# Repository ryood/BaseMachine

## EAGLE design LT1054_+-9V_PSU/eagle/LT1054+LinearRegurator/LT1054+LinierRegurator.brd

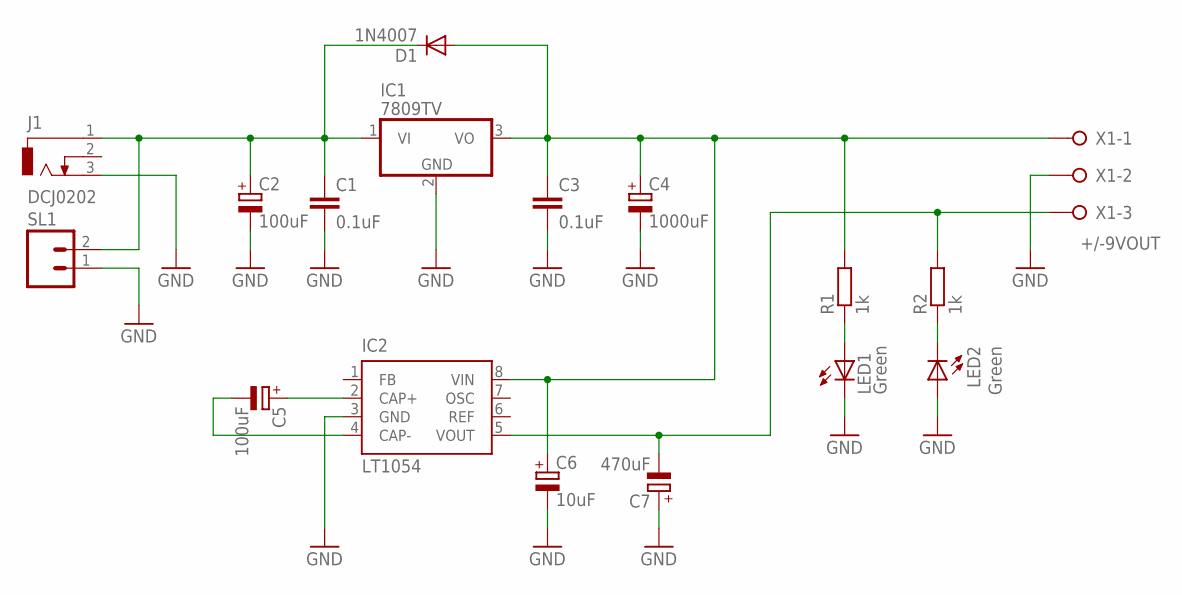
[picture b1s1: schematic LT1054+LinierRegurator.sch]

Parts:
C1, C3: 0.1uF; C025-024X044
C2, C5: 100uF; E2,5-7
C4: 1000uF; E5-13
C6: 10uF; E2,5-5
C7: 470uF; E5-8,5
D1: 1N4007; DO41-10
IC1: 7809TV; TO220V
IC2: LT1054; DIL8
J1: DCJ0202
LED1, LED2: Green; LED3MM
R1, R2: 1k; 0207/7
SL1: M02; 02P
X1: +/-9VOUT; W237-3E

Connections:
GND: C1.2, C2.-, C3.2, C4.-, C6.-, C7.+, IC1.2 (GND), IC2.3 (GND), J1.3, LED1.K (C), LED2.A, SL1.1, X1.2
unnamed: C1.1, C2.+, D1.C, IC1.1 (VI), J1.1, SL1.2
unnamed: C3.1, C4.+, C6.+, D1.A, IC1.3 (VO), IC2.8 (VIN), R1.2, X1.1
unnamed: C5.-, IC2.4 (CAP-)
unnamed: C5.+, IC2.2 (CAP+)
unnamed: C7.-, IC2.5 (VOUT), R2.2, X1.3
unnamed: LED1.A, R1.1
unnamed: LED2.K (C), R2.1

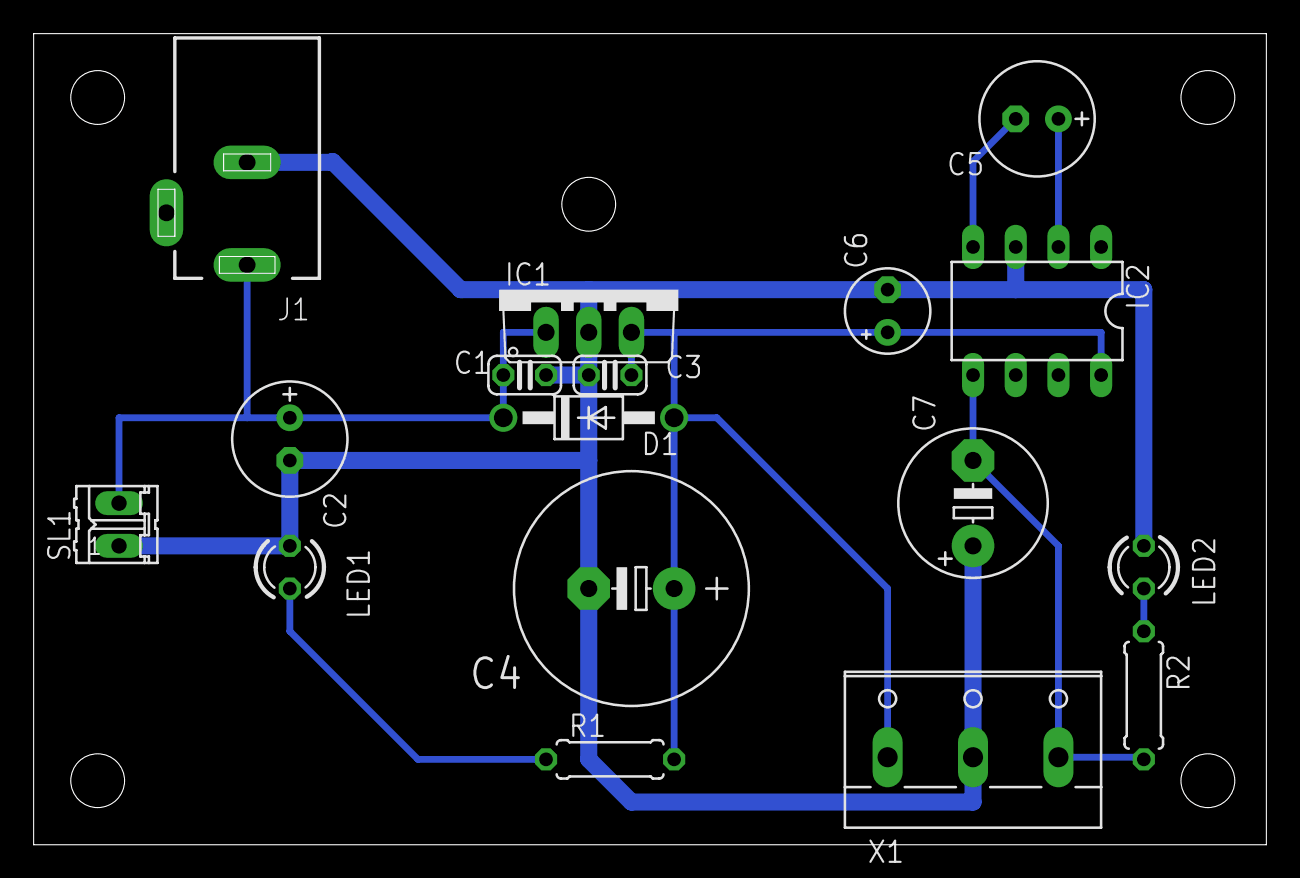
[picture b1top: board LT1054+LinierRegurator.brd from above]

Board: 2 copper layers, 73.3 x 48.2 mm, 17 parts (0 on the bottom side), 8 nets.

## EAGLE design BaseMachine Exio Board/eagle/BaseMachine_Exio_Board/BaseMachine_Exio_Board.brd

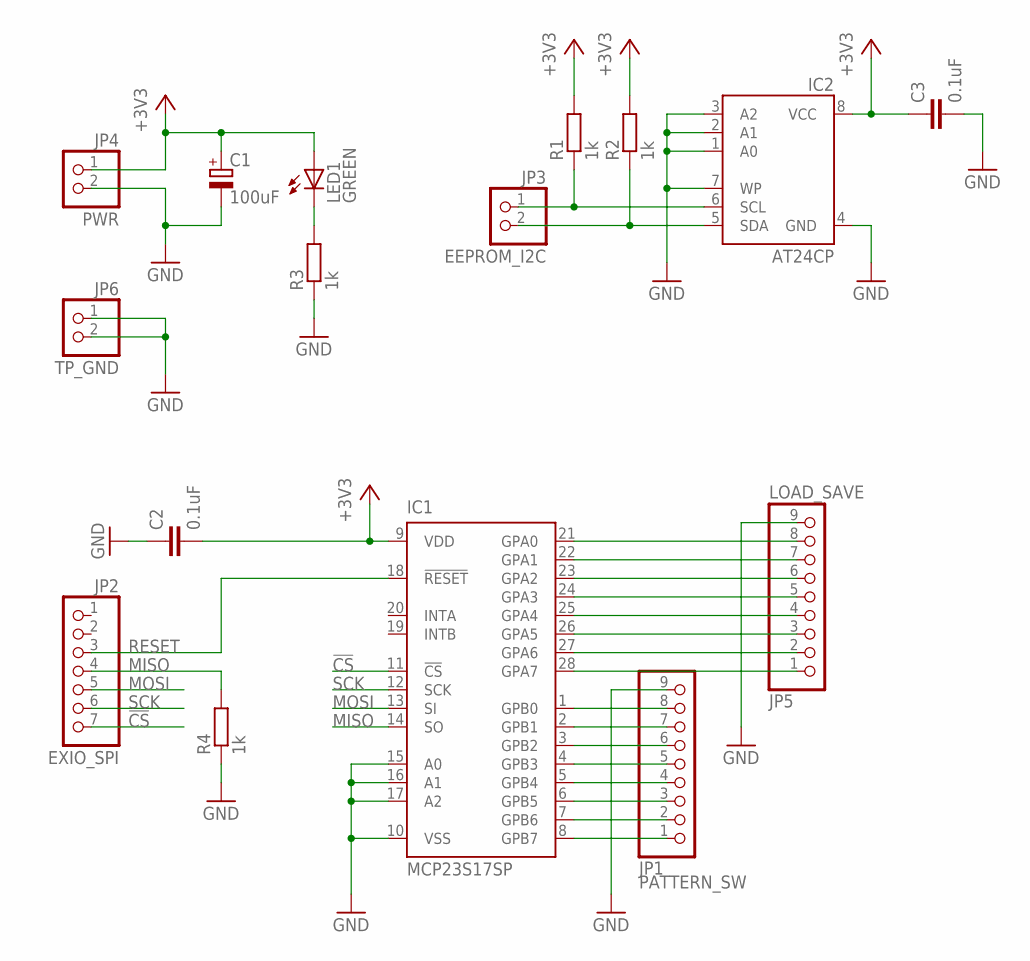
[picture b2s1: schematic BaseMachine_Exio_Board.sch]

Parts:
C1: 100uF; SANYO-OSCON_C6
C2, C3: 0.1uF; C025-024X044
IC1: MCP23S17SP; DIL28-3
IC2: AT24CP; DIL08
JP1: PATTERN_SW; 1X09/90
JP2: EXIO_SPI; 1X07/90
JP3: EEPROM_I2C; 1X02/90
JP4: PWR; 1X02/90
JP5: LOAD_SAVE; 1X09/90
JP6: TP_GND; 1X02
LED1: GREEN; LED3MM
R1, R2, R3, R4: 1k; 0207/7

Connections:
!CS: IC1.11 (!CS), JP2.7
+3V3: C1.+, C2.2, C3.1, IC1.9 (VDD), IC2.8 (VCC), JP4.1, LED1.A, R1.2, R2.2
GND: C1.-, C2.1, C3.2, IC1.10 (VSS), IC1.15 (A0), IC1.16 (A1), IC1.17 (A2), IC2.1 (A0), IC2.2 (A1), IC2.3 (A2), IC2.4 (GND), IC2.7 (WP), JP1.9, JP4.2, JP5.9, JP6.1, JP6.2, R3.1, R4.1
MISO: IC1.14 (SO), JP2.4, R4.2
MOSI: IC1.13 (SI), JP2.5
unnamed: IC1.1 (GPB0), JP1.8
unnamed: IC1.2 (GPB1), JP1.7
unnamed: IC1.3 (GPB2), JP1.6
unnamed: IC1.4 (GPB3), JP1.5
unnamed: IC1.5 (GPB4), JP1.4
unnamed: IC1.6 (GPB5), JP1.3
unnamed: IC2.6 (SCL), JP3.1, R1.1
unnamed: IC2.5 (SDA), JP3.2, R2.1
unnamed: IC1.7 (GPB6), JP1.2
unnamed: IC1.21 (GPA0), JP5.8
unnamed: IC1.22 (GPA1), JP5.7
unnamed: IC1.23 (GPA2), JP5.6
unnamed: IC1.8 (GPB7), JP1.1
unnamed: IC1.24 (GPA3), JP5.5
unnamed: IC1.25 (GPA4), JP5.4
unnamed: IC1.26 (GPA5), JP5.3
unnamed: LED1.K (C), R3.2
unnamed: IC1.27 (GPA6), JP5.2
unnamed: IC1.28 (GPA7), JP5.1
RESET: IC1.18 (!RESET), JP2.3
SCK: IC1.12 (SCK), JP2.6

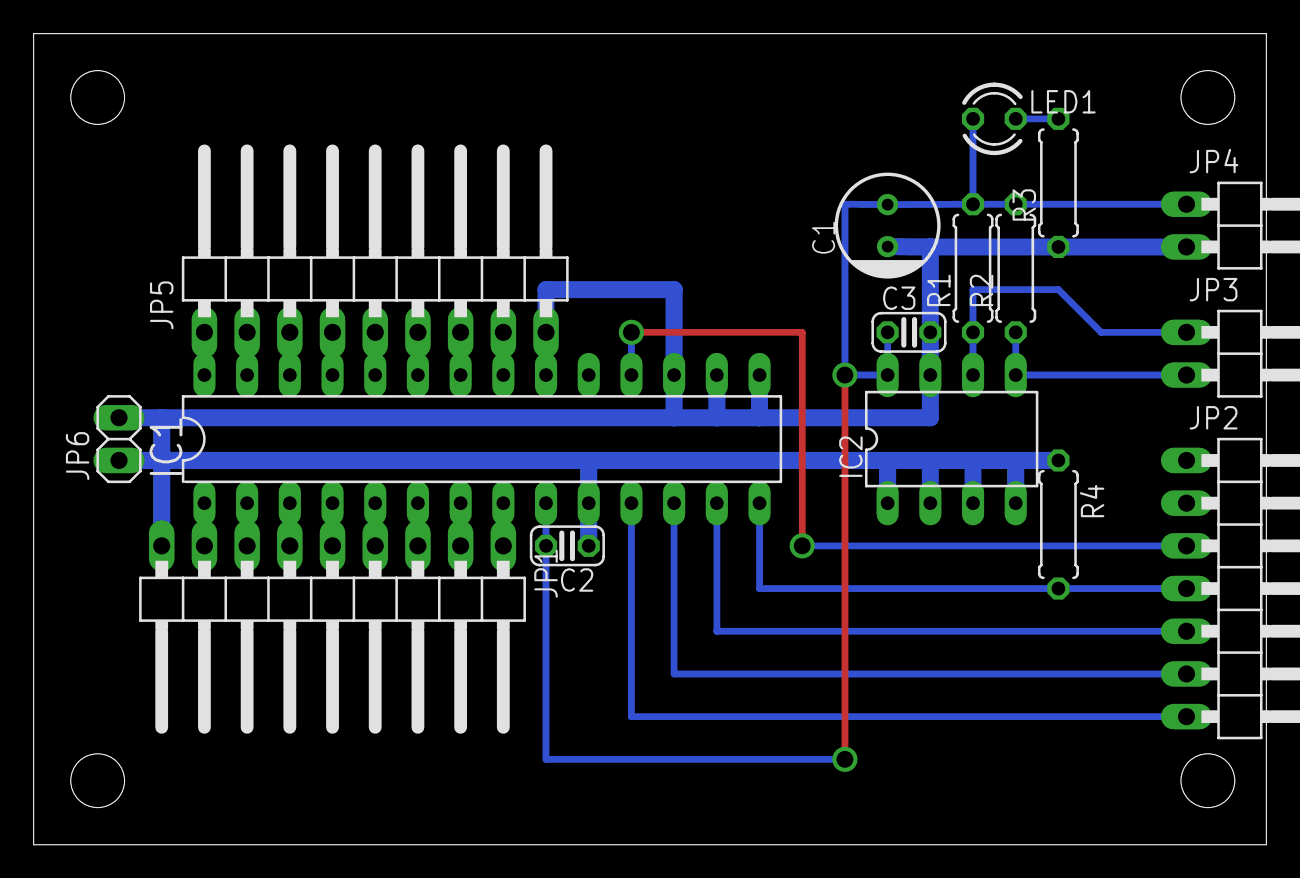
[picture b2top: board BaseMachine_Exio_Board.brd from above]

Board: 2 copper layers, 73.3 x 48.2 mm, 16 parts (0 on the bottom side), 26 nets.

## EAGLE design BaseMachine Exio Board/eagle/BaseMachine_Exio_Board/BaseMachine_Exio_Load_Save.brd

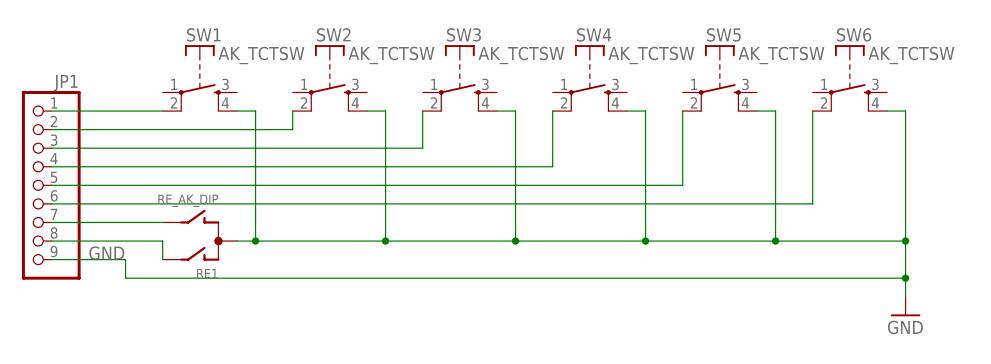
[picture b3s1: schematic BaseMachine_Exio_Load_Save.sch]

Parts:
JP1: PINHD-1X9; 1X09
RE1: RE_AK_DIP
SW1, SW2, SW3, SW4, SW5, SW6: AK_TCTSW; TME1

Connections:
GND: JP1.9, RE1.P$3 (C), SW1.4 (S), SW2.4 (S), SW3.4 (S), SW4.4 (S), SW5.4 (S), SW6.4 (S)
unnamed: JP1.1, SW1.2
unnamed: JP1.2, SW2.2
unnamed: JP1.3, SW3.2
unnamed: JP1.4, SW4.2
unnamed: JP1.5, SW5.2
unnamed: JP1.6, SW6.2
unnamed: JP1.7, RE1.P$4 (B)
unnamed: JP1.8, RE1.P$2 (A)

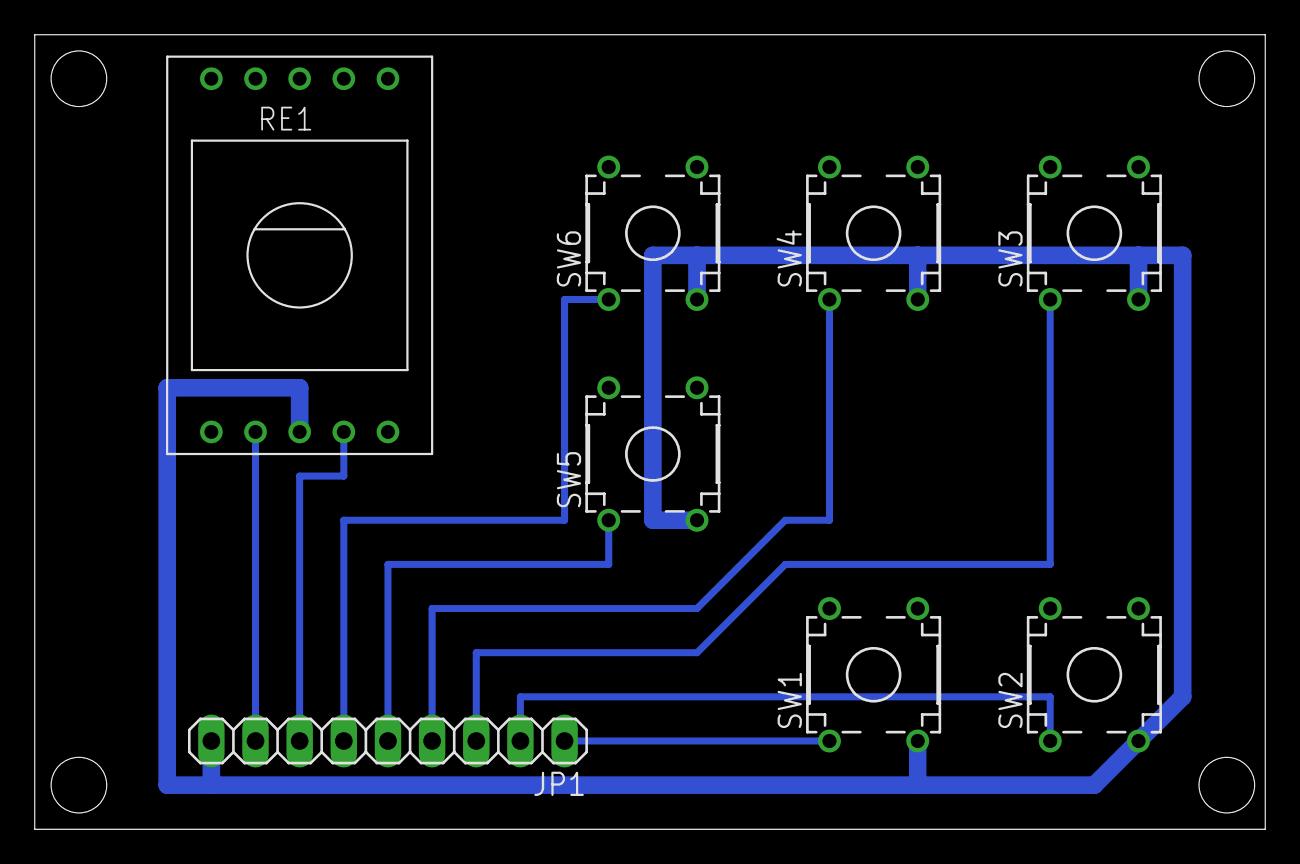
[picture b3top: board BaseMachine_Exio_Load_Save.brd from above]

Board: 2 copper layers, 70.8 x 45.7 mm, 8 parts (0 on the bottom side), 9 nets.

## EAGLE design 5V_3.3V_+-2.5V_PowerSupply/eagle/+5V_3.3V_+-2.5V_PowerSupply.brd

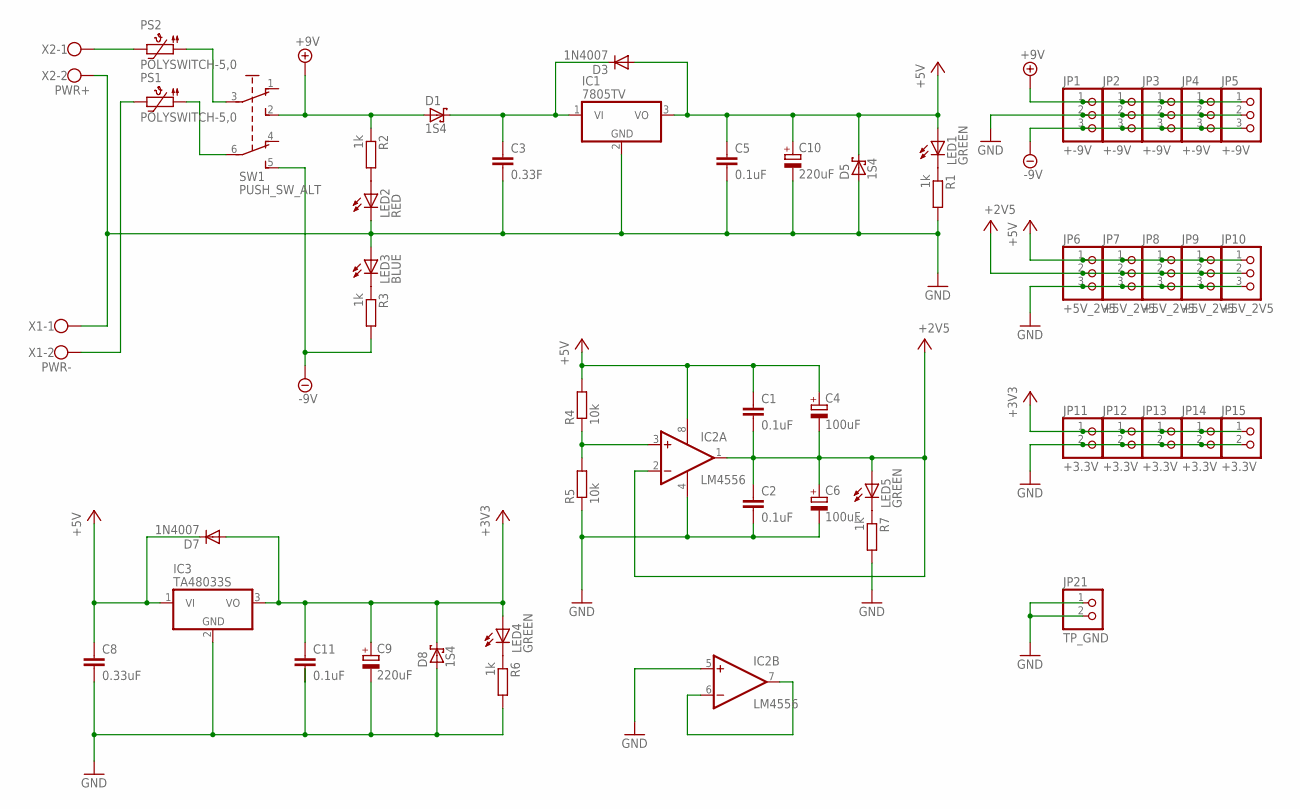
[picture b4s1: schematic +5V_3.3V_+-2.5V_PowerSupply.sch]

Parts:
C1, C2, C5, C11: 0.1uF; C025-024X044
C3: 0.33F; C050-025X075
C4, C6: 100uF; E2,5-6
C8: 0.33uF; C050-025X075
C9, C10: 220uF; E2,5-7
D1, D5, D8: 1S4; DO35-7
D3, D7: 1N4007; D-7.5
IC1: 7805TV; TO220V
IC2: LM4556; DIL08
IC3: TA48033S; TO220V
JP1, JP2, JP3, JP4, JP5: +-9V; 1X03
JP6, JP7, JP8, JP9, JP10: +5V_2V5; 1X03
JP11, JP12, JP13, JP14, JP15: +3.3V; 1X02
JP21: TP_GND; 1X02
LED1, LED4, LED5: GREEN; LED3MM
LED2: RED; LED3MM
LED3: BLUE; LED3MM
PS1, PS2: POLYSWITCH-5,0
R1, R2, R3, R6, R7: 1k; 0207/7
R4, R5: 10k; 0207/7
SW1: PUSH_SW_ALT
X1: PWR-; W237-102
X2: PWR+; W237-102

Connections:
+3V3: C9.+, C11.1, D7.A, D8.C, IC3.3 (VO), JP11.1, JP12.1, JP13.1, JP14.1, JP15.1, LED4.A
+5V: C1.1, C4.+, C5.1, C8.1, C10.+, D3.A, D5.C, D7.C, IC1.3 (VO), IC2.8 (V+), IC3.1 (VI), JP6.1, JP7.1, JP8.1, JP9.1, JP10.1, LED1.A, R4.2
+9V: D1.A, JP1.1, JP2.1, JP3.1, JP4.1, JP5.1, R2.1, SW1.2 (S)
-9V: JP1.3, JP2.3, JP3.3, JP4.3, JP5.3, R3.2, SW1.5 (S1)
GND: C2.2, C3.2, C5.2, C6.-, C8.2, C9.-, C10.-, C11.2, D5.A, D8.A, IC1.2 (GND), IC2.4 (V-), IC2.5 (+IN), IC3.2 (GND), JP1.2, JP2.2, JP3.2, JP4.2, JP5.2, JP6.3, JP7.3, JP8.3, JP9.3, JP10.3, JP11.2, JP12.2, JP13.2, JP14.2, JP15.2, JP21.1, JP21.2, LED2.K (C), LED3.A, R1.2, R5.1, R6.2, R7.2, X1.1, X2.2
unnamed: PS2.2, X2.1
unnamed: PS1.1, SW1.6 (P1)
unnamed: LED1.K (C), R1.1
unnamed: LED2.A, R2.2
unnamed: C3.1, D1.C, D3.C, IC1.1 (VI)
unnamed: LED3.K (C), R3.1
unnamed: IC2.3 (+IN), R4.1, R5.2
unnamed: LED5.K (C), R7.1
unnamed: IC2.6 (-IN), IC2.7 (OUT)
unnamed: PS1.2, X1.2
unnamed: PS2.1, SW1.3
unnamed: LED4.K (C), R6.1
V+: C1.2, C2.1, C4.-, C6.+, IC2.1 (OUT), IC2.2 (-IN), JP6.2, JP7.2, JP8.2, JP9.2, JP10.2, LED5.A

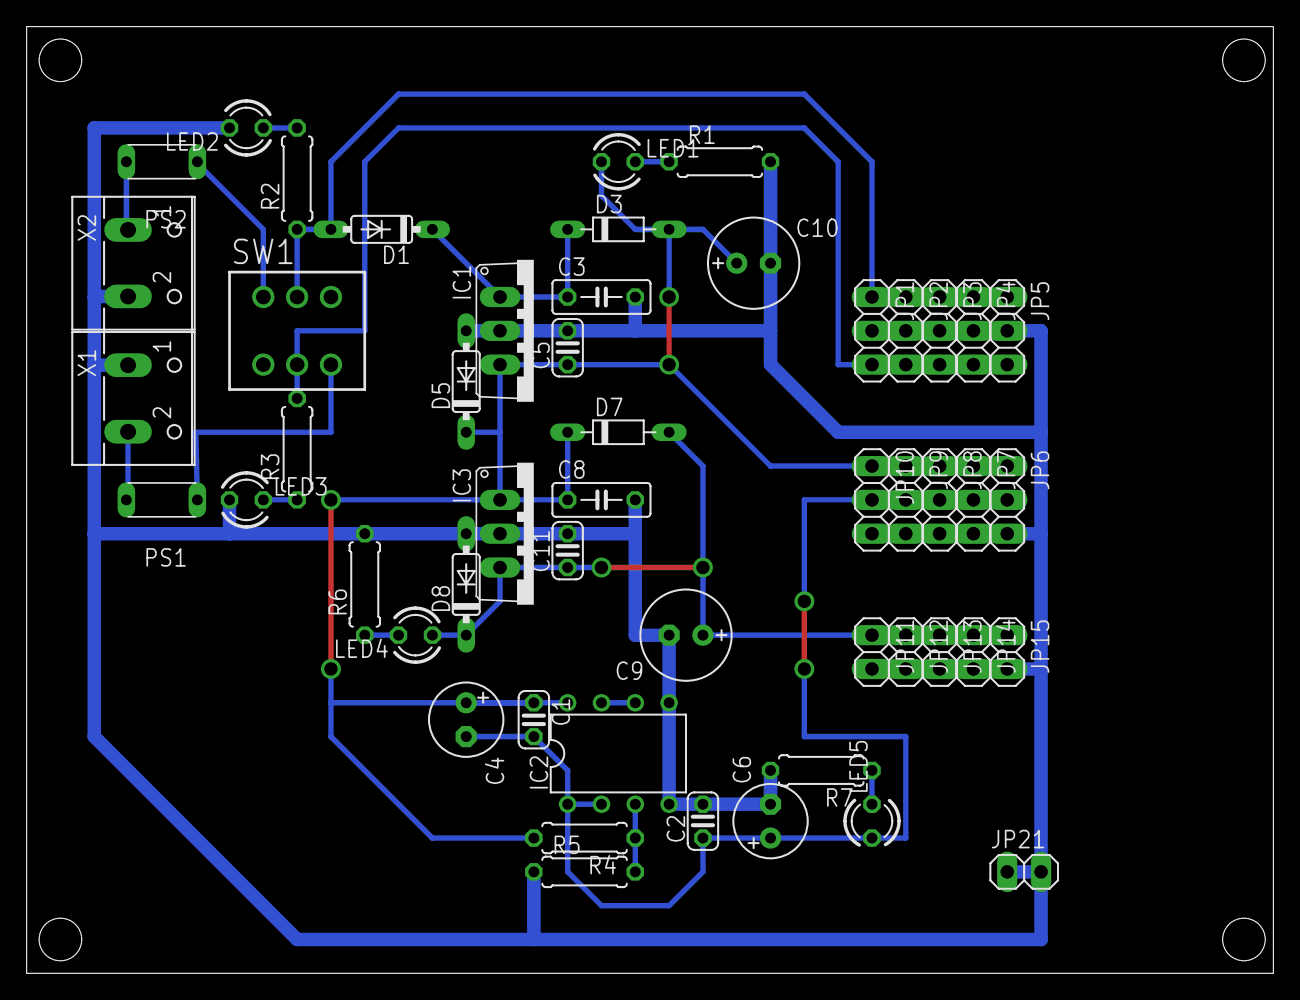
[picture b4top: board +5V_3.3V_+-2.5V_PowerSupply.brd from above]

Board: 2 copper layers, 93.7 x 71.1 mm, 51 parts (0 on the bottom side), 18 nets.

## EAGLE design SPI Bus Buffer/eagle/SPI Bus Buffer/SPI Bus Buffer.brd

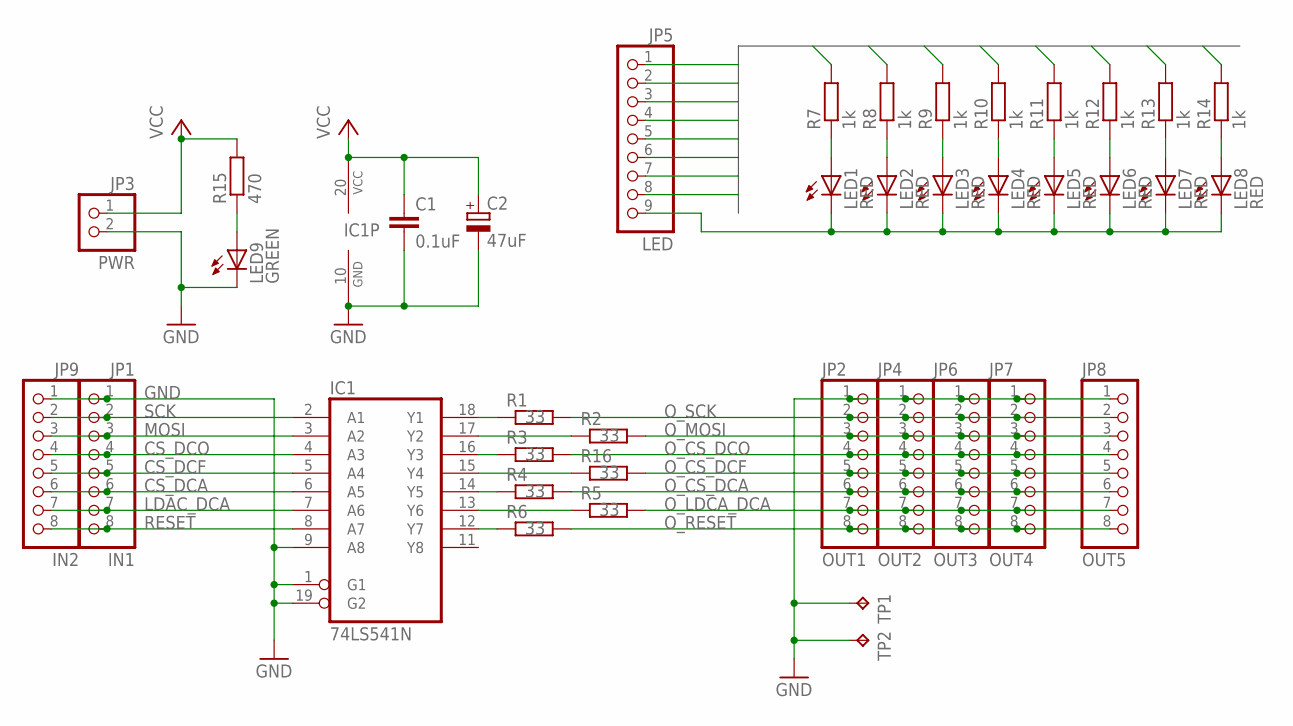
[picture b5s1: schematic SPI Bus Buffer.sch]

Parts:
C1: 0.1uF; C050-024X044
C2: 47uF; E2,5-5
IC1: 74LS541N; DIL20
JP1: IN1; 1X08
JP2: OUT1; 1X08
JP3: PWR; 1X02
JP4: OUT2; 1X08
JP5: LED; 1X09
JP6: OUT3; 1X08
JP7: OUT4; 1X08
JP8: OUT5; 1X08
JP9: IN2; 1X08
LED1, LED2, LED3, LED4, LED5, LED6, LED7, LED8: RED; LED3MM
LED9: GREEN; LED3MM
R1, R2, R3, R4, R5, R6, R16: 33; 0207/7
R7, R8, R9, R10, R11, R12, R13, R14: 1k; 0207/7
R15: 470; 0207/7
TP1, TP2: TPPAD1-13; P1-13

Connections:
CS_DCA: IC1.6 (A5), JP1.6, JP9.6
CS_DCF: IC1.5 (A4), JP1.5, JP9.5
CS_DCO: IC1.4 (A3), JP1.4, JP9.4
GND: C1.2, C2.-, IC1.1 (G1), IC1.9 (A8), IC1.10 (GND), IC1.19 (G2), JP1.1, JP2.1, JP3.2, JP4.1, JP6.1, JP7.1, JP8.1, JP9.1, LED9.K (C), TP1.TP, TP2.TP
LDAC_DCA: IC1.7 (A6), JP1.7, JP9.7
LEDS1: JP5.1, R7.2
LEDS2: JP5.2, R8.2
LEDS3: JP5.3, R9.2
LEDS4: JP5.4, R10.2
LEDS5: JP5.5, R11.2
LEDS6: JP5.6, R12.2
LEDS7: JP5.7, R13.2
LEDS8: JP5.8, R14.2
MOSI: IC1.3 (A2), JP1.3, JP9.3
unnamed: IC1.18 (Y1), R1.1
unnamed: IC1.17 (Y2), R2.1
unnamed: IC1.16 (Y3), R3.1
unnamed: IC1.14 (Y5), R4.1
unnamed: IC1.13 (Y6), R5.1
unnamed: IC1.12 (Y7), R6.1
unnamed: LED1.A, R7.1
unnamed: LED2.A, R8.1
unnamed: LED3.A, R9.1
unnamed: LED4.A, R10.1
unnamed: LED5.A, R11.1
unnamed: LED6.A, R12.1
unnamed: LED7.A, R13.1
unnamed: LED8.A, R14.1
unnamed: LED9.A, R15.1
unnamed: IC1.15 (Y4), R16.1
unnamed: JP5.9, LED1.K (C), LED2.K (C), LED3.K (C), LED4.K (C), LED5.K (C), LED6.K (C), LED7.K (C), LED8.K (C)
O_CS_DCA: JP2.6, JP4.6, JP6.6, JP7.6, JP8.6, R4.2
O_CS_DCF: JP2.5, JP4.5, JP6.5, JP7.5, JP8.5, R16.2
O_CS_DCO: JP2.4, JP4.4, JP6.4, JP7.4, JP8.4, R3.2
O_LDCA_DCA: JP2.7, JP4.7, JP6.7, JP7.7, JP8.7, R5.2
O_MOSI: JP2.3, JP4.3, JP6.3, JP7.3, JP8.3, R2.2
O_RESET: JP2.8, JP4.8, JP6.8, JP7.8, JP8.8, R6.2
O_SCK: JP2.2, JP4.2, JP6.2, JP7.2, JP8.2, R1.2
RESET: IC1.8 (A7), JP1.8, JP9.8
SCK: IC1.2 (A1), JP1.2, JP9.2
VCC: C1.1, C2.+, IC1.20 (VCC), JP3.1, R15.2

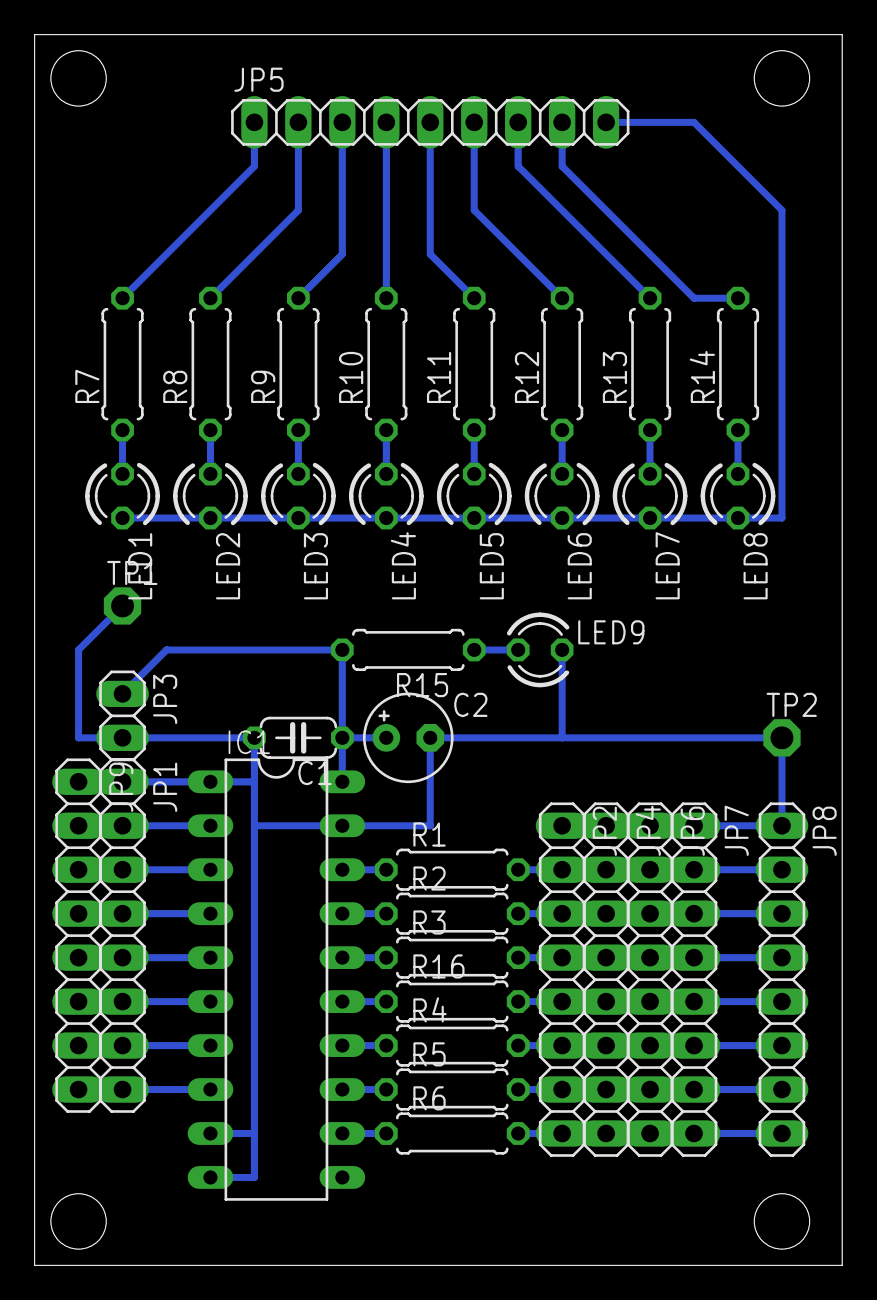
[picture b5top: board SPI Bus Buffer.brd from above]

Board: 2 copper layers, 46.7 x 71.1 mm, 39 parts (0 on the bottom side), 41 nets.

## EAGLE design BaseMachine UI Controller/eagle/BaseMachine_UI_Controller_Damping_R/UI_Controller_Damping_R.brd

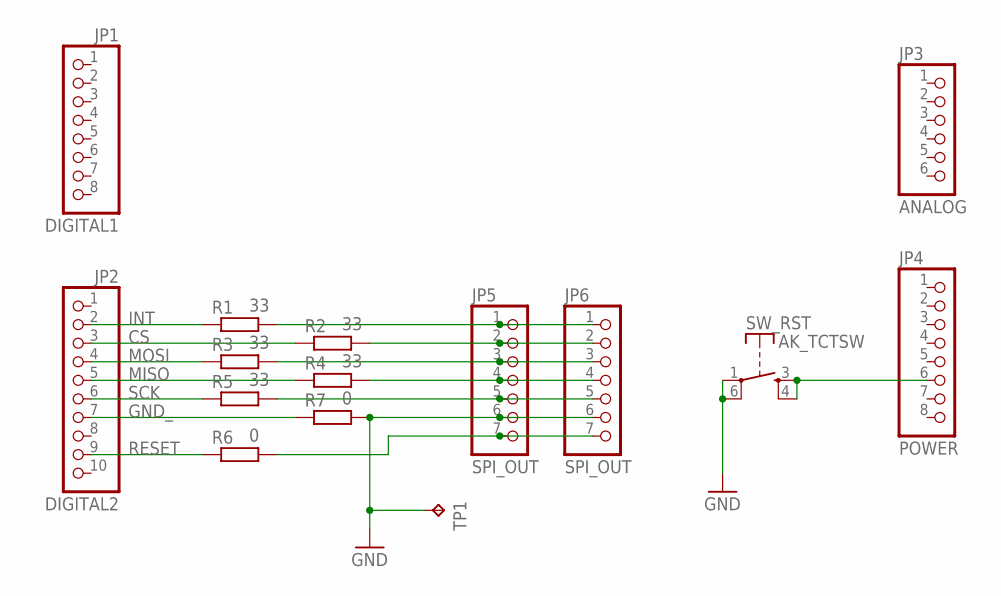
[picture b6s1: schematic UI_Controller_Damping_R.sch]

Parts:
JP1: DIGITAL1; 1X08
JP2: DIGITAL2; 1X10
JP3: ANALOG; 1X06
JP4: POWER; 1X08
JP5, JP6: SPI_OUT; 1X07
R1, R2, R3, R4, R5: 33; 0207/7
R6, R7: 0; 0207/7
SW_RST: AK_TCTSW; TME1
TP1: TPPAD1-13; P1-13

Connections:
CS: JP2.3, R2.1
GND: JP5.6, JP6.6, R7.2, SW_RST.1, SW_RST.6, TP1.TP
GND_: JP2.7, R7.1
INT: JP2.2, R1.1
MISO: JP2.5, R4.1
MOSI: JP2.4, R3.1
unnamed: JP5.1, JP6.1, R1.2
unnamed: JP5.2, JP6.2, R2.2
unnamed: JP5.3, JP6.3, R3.2
unnamed: JP5.4, JP6.4, R4.2
unnamed: JP5.5, JP6.5, R5.2
unnamed: JP5.7, JP6.7, R6.2
unnamed: JP4.6, SW_RST.3 (S), SW_RST.4 (S)
RESET: JP2.9, R6.1
SCK: JP2.6, R5.1

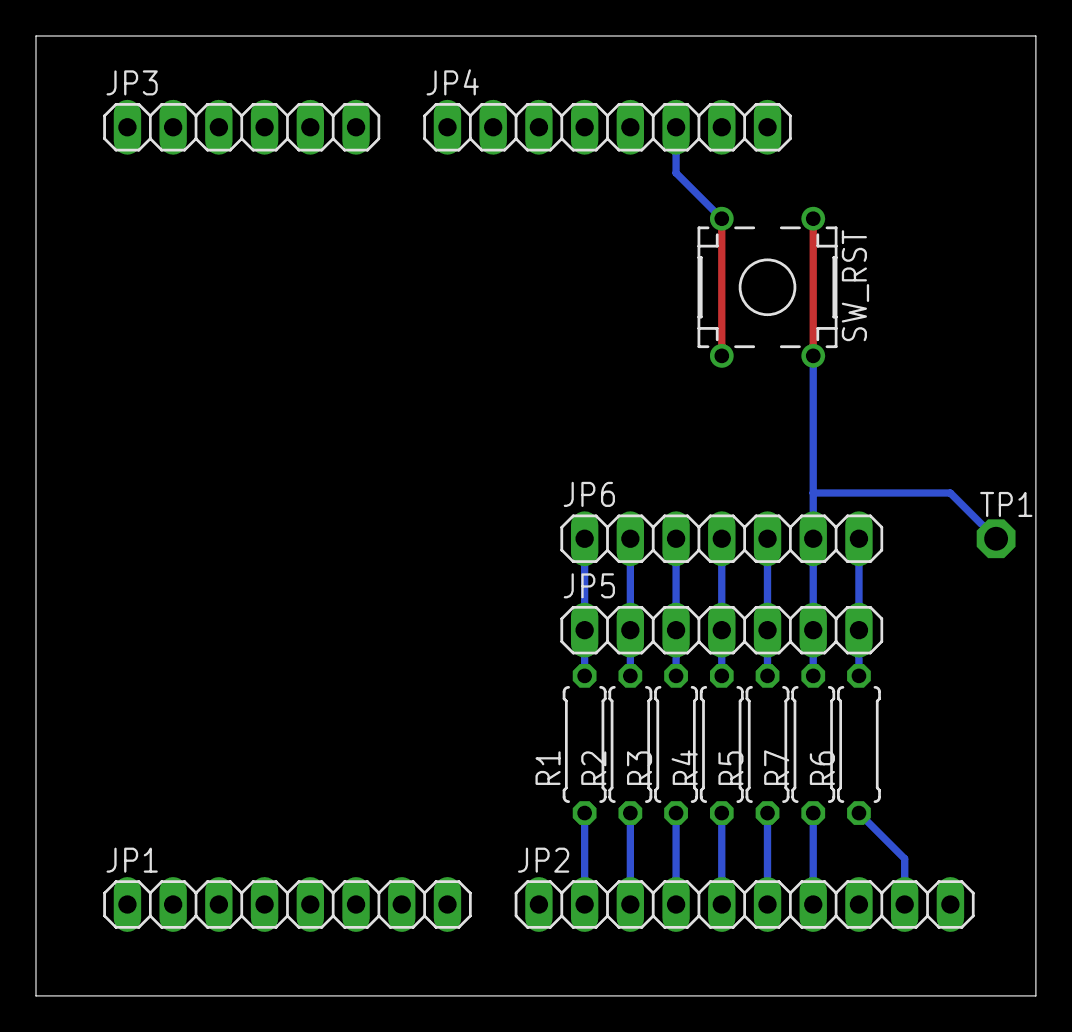
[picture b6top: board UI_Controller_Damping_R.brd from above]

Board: 2 copper layers, 55.5 x 53.3 mm, 15 parts (0 on the bottom side), 15 nets.

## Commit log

2016-10-07 Add: BaseMachine UI Controller
2016-10-16 Updated Documents
2016-10-16 Updated: Pins of RunStop & Step(RotEnc)
2016-10-16 Updated fritzing files
2016-10-16 Add: eagle files of the UI_Controller_Damping_R Shield
2016-10-16 Add: UI_Contorller_Damping_R_Shield
2016-10-20 Add: some holes on the BaseMachine Synth Panel
2016-10-23 Update: ベースマシン Sequencer SPIコマンド一覧
2016-10-25 Add: SPI Bus Buffer
2016-11-11 Update: Eagel files of the SPI Bus Buffer
2016-12-06 a bit
2016-12-19 Updated documents, clean up files
2016-12-23 Update: Documents
2016-12-23 Add: 5V_3.3V_2.5V_PowerSupply
2016-12-23 Update: 5V_3V3_2V5_PowerSupply Eagle Files
2016-12-25 Update: Eagle files
2016-12-25 clean up
2016-12-25 Update: Board design
2016-12-29 Add: 5V_3.3V_+-2.5V_PowerSupply Test Chart
2017-01-03 Add: BaseMachine Exio Board
2017-01-06 Update: BaseMachine Exio Board
2017-01-16 Add:BaseMachine ToDo.xlsx
2017-03-01 Update: Todo
2017-03-04 Updated: ベースマシン接続一覧表.xlsx
2017-04-04 Add: LT1054_+-9V_PSU
2017-04-04 Add: Image files
2017-04-10 Update: ベースマシン接続一覧表.xlsx
2017-04-22 Add BaseMchine chassis pannel dwg
2017-05-04 Update: BaseMachine ToDo
2017-08-18 Add Chassis Design
2017-08-23 updated: chassis drawing
2018-03-03 Add: まとめ その2
